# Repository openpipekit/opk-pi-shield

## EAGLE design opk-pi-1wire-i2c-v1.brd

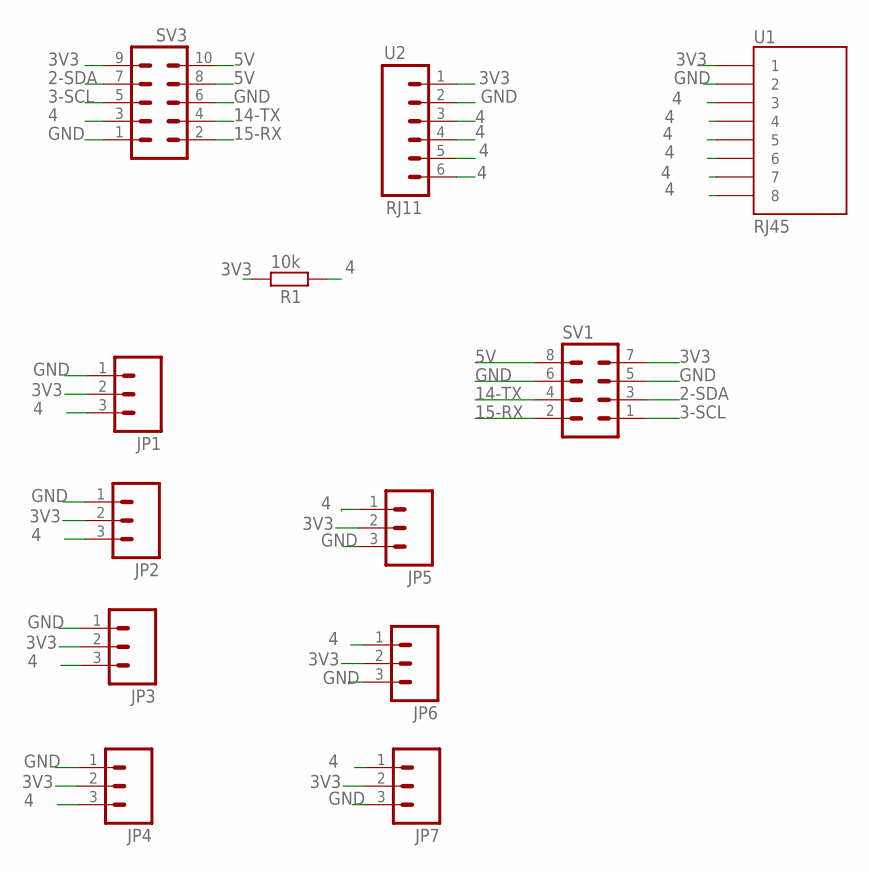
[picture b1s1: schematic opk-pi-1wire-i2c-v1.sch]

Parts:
JP1, JP2, JP3, JP4, JP5, JP6, JP7: M03SCREW; SCREWTERMINAL-3.5MM-3
R1: 10k; 0204/7
SV1: MA04-2
SV3: MA05-2
U1: RJ45; RJ45-8
U2: RJ11; RJ11-6

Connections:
2-SDA: SV1.3, SV3.7
3-SCL: SV1.1, SV3.5
3V3: JP1.2, JP2.2, JP3.2, JP4.2, JP5.2, JP6.2, JP7.2, R1.2, SV1.7, SV3.9, U1.1, U2.1
4: JP1.3, JP2.3, JP3.3, JP4.3, JP5.1, JP6.1, JP7.1, R1.1, SV3.3, U1.3, U1.4, U1.5, U1.6, U1.7, U1.8, U2.3, U2.4, U2.5, U2.6
5V: SV1.8, SV3.8, SV3.10
14-TX: SV1.4, SV3.4
15-RX: SV1.2, SV3.2
GND: JP1.1, JP2.1, JP3.1, JP4.1, JP5.3, JP6.3, JP7.3, SV1.5, SV1.6, SV3.1, SV3.6, U1.2, U2.2

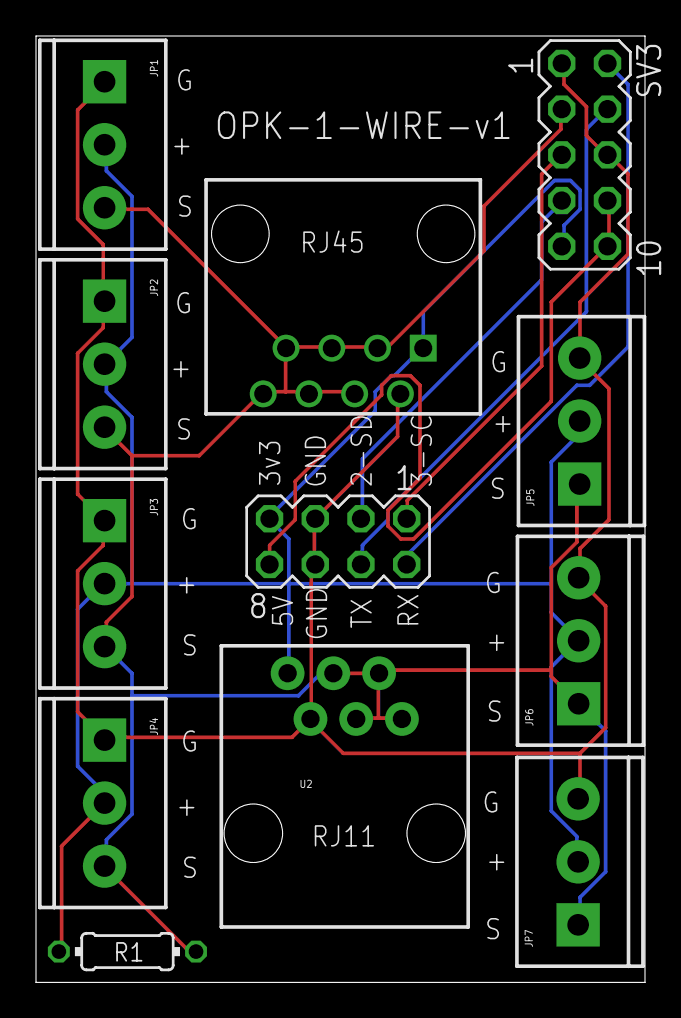
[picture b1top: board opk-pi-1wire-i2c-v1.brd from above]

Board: 2 copper layers, 33.8 x 52.6 mm, 12 parts (0 on the bottom side), 8 nets.

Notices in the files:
parts and their libraries:
SparkFun-Connectors: Licensing: Creative Commons ShareAlike 4.0 International - https://creativecommons.org/licenses/by-sa/4.0
